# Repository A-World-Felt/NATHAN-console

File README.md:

# NATHAN Console

## How it began

The NATHAN console was born from a desire to create something meaningful for an incredible person: **Nathan Therrien**.

I met Nathan in high school. He was one of those rare people who naturally brighten the world around them. Always smiling, always the first to say hello, to crack a joke, to make everyone around him feel good. We shared the same class in our final year, and even then, I was amazed by his radiant energy.

After high school, life took us in different directions. But I kept following Nathan online, especially through his Facebook page, where he shares videos of his musical explorations. Because yes, on top of everything else, **Nathan is an outstanding musician** and a passionate synthesizer enthusiast.

One morning in year 2022, Nathan made a post looking for help with 3D printing and soldering. At that time, I was just diving into the world of programming, microcontrollers, and digital fabrication. I was eager to learn and build something real. The moment I saw his message, I knew: **this was the project I had been waiting for**.

Working with Nathan, someone I had admired for years, gave me the perfect opportunity to grow my skills while collaborating with someone truly inspiring. He would be part of the process: designing the sounds, shaping the ideas, and even learning to code. From the start, the goal was clear: **build something together that he could one day fully own**.

Since 2022, this journey has become a shared adventure. Today, I’m proud to present the first version of the console:
**NATHAN — Narrative Audio Terminal for Humans with Alternative Navigation**.

As time becomes more limited for me, my hope is to pass the torch. I want the community to take this project further, to make it bigger, better, and even more inclusive.

---

## What is NATHAN?

**NATHAN** is an open source game console powered by a Raspberry Pi Pico, specifically designed for blind or visually impaired players.

Inspired by the form of an Xbox controller, the device includes:

* 5 tactile buttons
* 5 LED indicators
* An integrated audio output
  Together, these features enable an immersive and fully accessible gaming experience.

---

## Features

* 🎮 **Ergonomic form** – Inspired by the Xbox controller for comfortable use
* 🔘 **5 physical buttons** – Easily distinguishable for gameplay
* 💡 **5 LED indicators** – Optional visual feedback
* 🔊 **Audio output** – For immersive, sound-based gameplay
* ♿ **Inclusive game design** – Every game is made for accessibility

---

## Game Concept

Each game on the NATHAN console features a **blind protagonist named Nathan**.

The current flagship game, **NATHAN: Glassbreaker**, puts you in the role of Nathan, a hero who fights and navigates *only* through sound. It's a game where your ears become your eyes, and audio becomes your primary interface with the world. A game felt instead of seen.

---

## Open Source & Community

NATHAN is proudly open source.

This project is a call to creators, developers, makers, and dreamers:
**Let’s build accessible games together.**

Whether you want to:

* Design new games tailored for blind players
* Improve the hardware or firmware
* Suggest ideas to enhance the console
  Your contribution is welcome.

---

## Name Meaning

> **NATHAN** = *Narrative Audio Terminal for Humans with Alternative Navigation*

A console built around sound, for a hero and a community that navigates the world differently.

---

> 🎙️ *Together, let’s make gaming accessible to everyone.*

---

## 📚 Documentation & gouvernance

Toute la documentation projet vit dans [`docs/`](./docs/) :

- **[`docs/README.md`](./docs/README.md)** — *commencez ici* (parcours de lecture).
- **[Journal des décisions — ADR](./docs/decisions/README.md)** — *pourquoi* le projet est ainsi, et son évolution dans le temps.
- **[Specs](./docs/specs/)** · **[Planification & GANTT](./docs/planning/)** · **[Architecture](./docs/architecture/)**.
- **[CONTRIBUTING.md](./CONTRIBUTING.md)** — comment contribuer et **tracer une décision**.
- **[Étude matérielle Pi 3 A+ / deux PCB](./hardware/pi3a-prototype/README.md)** — proposition Codex en cours de revue, avec schémas et placements ; statut exact des validations indiqué dans le dossier.

---

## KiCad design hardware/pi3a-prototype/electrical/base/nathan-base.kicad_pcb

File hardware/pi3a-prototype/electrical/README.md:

> État figé et résultats de référence : [README D1-3](../README.md). Les points de conception ci-dessous restent des propositions, distinctes des essais matériels.

# Schémas D1 — connexions proposées pour revue

Auteur : Codex/OpenAI `nathan_bom`. Les projets `controls/nathan-controls.kicad_pro` et `base/nathan-base.kicad_pro` contiennent des schémas KiCad 8 éditables. Les symboles fonctionnels locaux portent des broches numérotées ; leurs connexions sont nommées explicitement. `design-networks.json`, `pin-map.csv` et `bom-proposal.csv` détaillent la source et la limite de chaque proposition.

La carte commandes comprend **93 composants physiques proposés et 4 déclarations ERC**, répartis entre interface, entrées numériques, entrées analogiques, multiplexeur, cinq branches haptiques et buck. Son ERC natif actuel rapporte **0 violation**. L’export natif initial, comparé au modèle broche par broche, ne présentait aucune connexion divergente ou absente. Un ERC réussi ne remplace ni la vérification du dessin fabricant, ni le dimensionnement thermique, ni les essais du matériel.

La porteuse D1 comprend **88 composants physiques proposés**, dont circuits audio et USB-C ; leur qualification reste à faire. Les nets `USB_PC_VBUS`, `USB_CHARGE_LIMITED` et `5V_SYS` restent distincts. Aucun fil artificiel ne remplace les protections et contrôles manquants. Le projet PCB D0.1 est une étude de placement séparée : **le checkpoint D1-3 comporte des commandes routées et une porteuse placée avec 257 liaisons encore ouvertes**.

## Choix proposés à partir des données connues

| Choix D1 | Motif et limite |
|---|---|
| MCP3208-CI/SL à la place du MCP3008 | Résolution 12 bits conforme au texte du cahier des charges. Brochage SOIC-16 vérifié ; trames SPI/logiciel à adapter. Ce remplacement n’est pas effectué dans le classeur original. |
| L2/R2 analogiques | Variante cohérente avec les deux potentiomètres envisagés dans le BOM ; elle conserve 14 entrées numériques avec L1/R1 et les clics des sticks. Technologie mécanique/capteur à sélectionner. |
| MCP23017-E/SO, 14 entrées seulement | Les broches GPA7/GPB7 restent inutilisées comme entrées ; configuration en sorties basses prévue. INTA porte l’interruption miroir ; INTB reste libre. |
| TCA9548APWR, adresse 0x70 | Cinq branches pour les cinq DRV2604L à 0x5A ; une branche sélectionnée par transaction. |
| DRV2604LDGSR | Brochage DGS vérifié. REG et VDD découplés, IN/TRIG à la masse, EN au rail haptique ; chaque moteur reste connecté entre les deux sorties différentielles. |
| Logique sur 3V3_PI, moteurs sur buck séparé | Aucun parallélisme entre régulateurs 3,3 V. Les pull-up aval suivent le rail moteur ; séquencement des alimentations encore à vérifier. |
| TPS62080DSGR conservé | Diviseur 249 kΩ/39,2 kΩ : 3,308 V nominal. Inductance 1 µH et condensateurs selon l’application TI, avec qualification des références/dérating encore requise. |
| Nappe GPIO polarisée | La porteuse inférieure ne peut pas être supposée enfichable sous le Pi : le PiSugar occupe cette zone par ses contacts pogo et le GPIO du Pi est dirigé vers le haut. La nappe préserve démontabilité et séparation des supports. |

Les broches 15/16 du connecteur intercartes D1 deviennent `3V3_PI` et `CTRL_RESET_N` ; elles étaient réservées dans D0.1. Ne pas fabriquer ni mélanger une nappe et une carte à partir de révisions différentes. Le fichier historique `pcb/interboard-interface.csv` décrit encore D0 ; le contrat D1 fait foi dans `pin-map.csv`, références J100 des deux cartes.

Le démarrage logiciel doit configurer l’extension, les interruptions, la sélection du multiplexeur et le mode LRA. La consigne VG0832013D reste 1,8 Vrms ; alimenter le driver en 3,3 V ne définit pas sa consigne moteur. SPI à 100 kHz et conversion d’amorçage après changement de voie sont proposés pour qualifier le filtre d’entrée ; aucune précision effective de 12 bits n’est garantie par le seul nombre de bits du composant.

## Sources vérifiées

- [Microchip MCP3208, DS21298E](https://ww1.microchip.com/downloads/en/DeviceDoc/21298e.pdf), tableau 3-1 page 15 et acquisition pages 17–18.
- [Microchip MCP23017, DS20001952D](https://ww1.microchip.com/downloads/aemDocuments/documents/APID/ProductDocuments/DataSheets/MCP23017-Data-Sheet-DS20001952.pdf), pages 1 et 11.
- [TI TCA9548A, SCPS207H](https://www.ti.com/lit/ds/symlink/tca9548a.pdf), brochage page 3.
- [TI DRV2604L, SLOS866F](https://www.ti.com/lit/ds/symlink/drv2604l.pdf), DGS page 4.
- [TI TPS62080, SLVSAE8F](https://www.ti.com/lit/ds/symlink/tps62080.pdf), pages 4, 12–14 et 19.

## Ce qu’il reste avant une carte complète

1. Qualifier les connecteurs/câbles et les références passives, terminer les empreintes de l’inductance et des commandes physiques.
2. Réaliser la chaîne casque, sa commande de volume/mute et son alimentation ; PCM5102A seul reste une sortie ligne.
3. Définir le circuit du port commun : courant d’entrée autorisé selon la source, blocage inverse, détection VBUS, protection ESD et raccordement USB périphérique du Pi.
4. Reporter la netlist finale aux PCB, adapter le placement, router puis vérifier chaque carte et sa correspondance au schéma.
5. Valider l’empilement réel et les mouvements dans l’assemblage, puis effectuer les essais électriques/thermiques/USB/autonomie.

Les éléments bloqués sont précisément visibles dans les connecteurs et notes du schéma. Ils ne sont ni masqués par des réserves présentées comme pièces réelles ni remplacés par des pistes arbitraires.

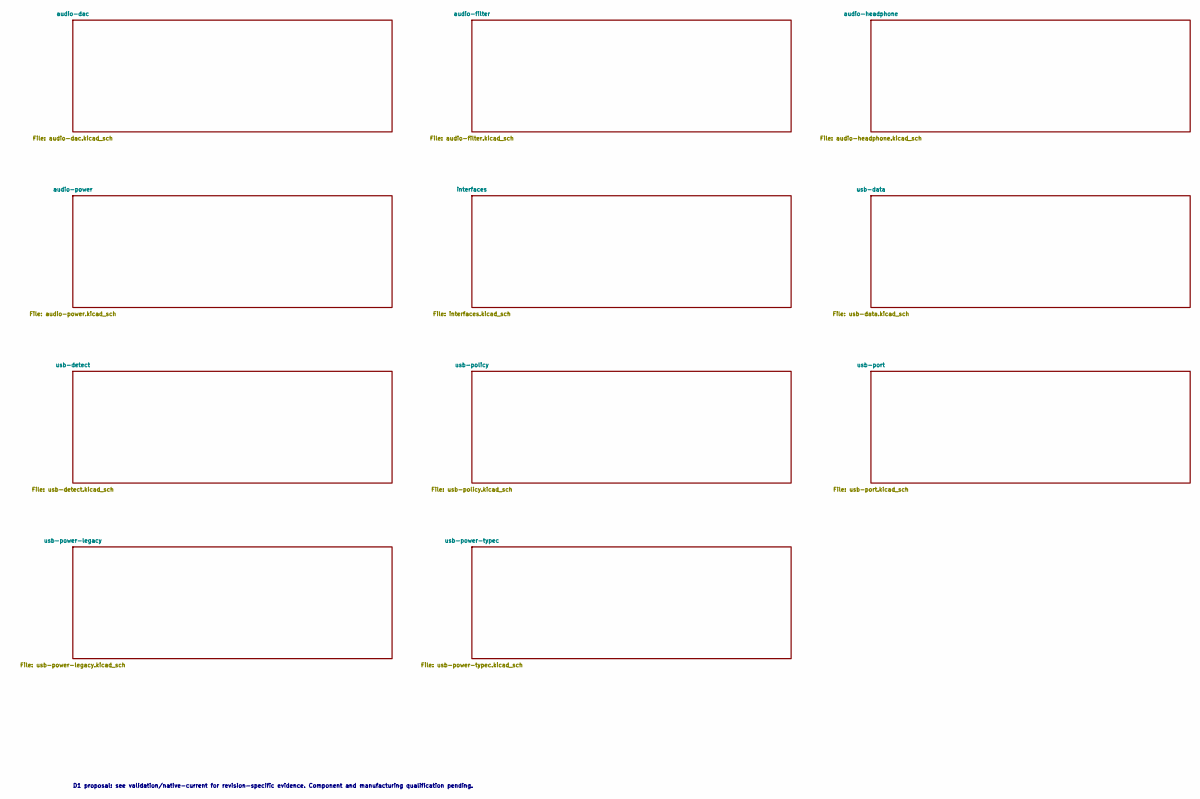
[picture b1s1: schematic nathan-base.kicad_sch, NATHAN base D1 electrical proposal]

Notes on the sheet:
D1 proposal: see validation/native-current for revision-specific evidence. Component and manufacturing qualification pending.

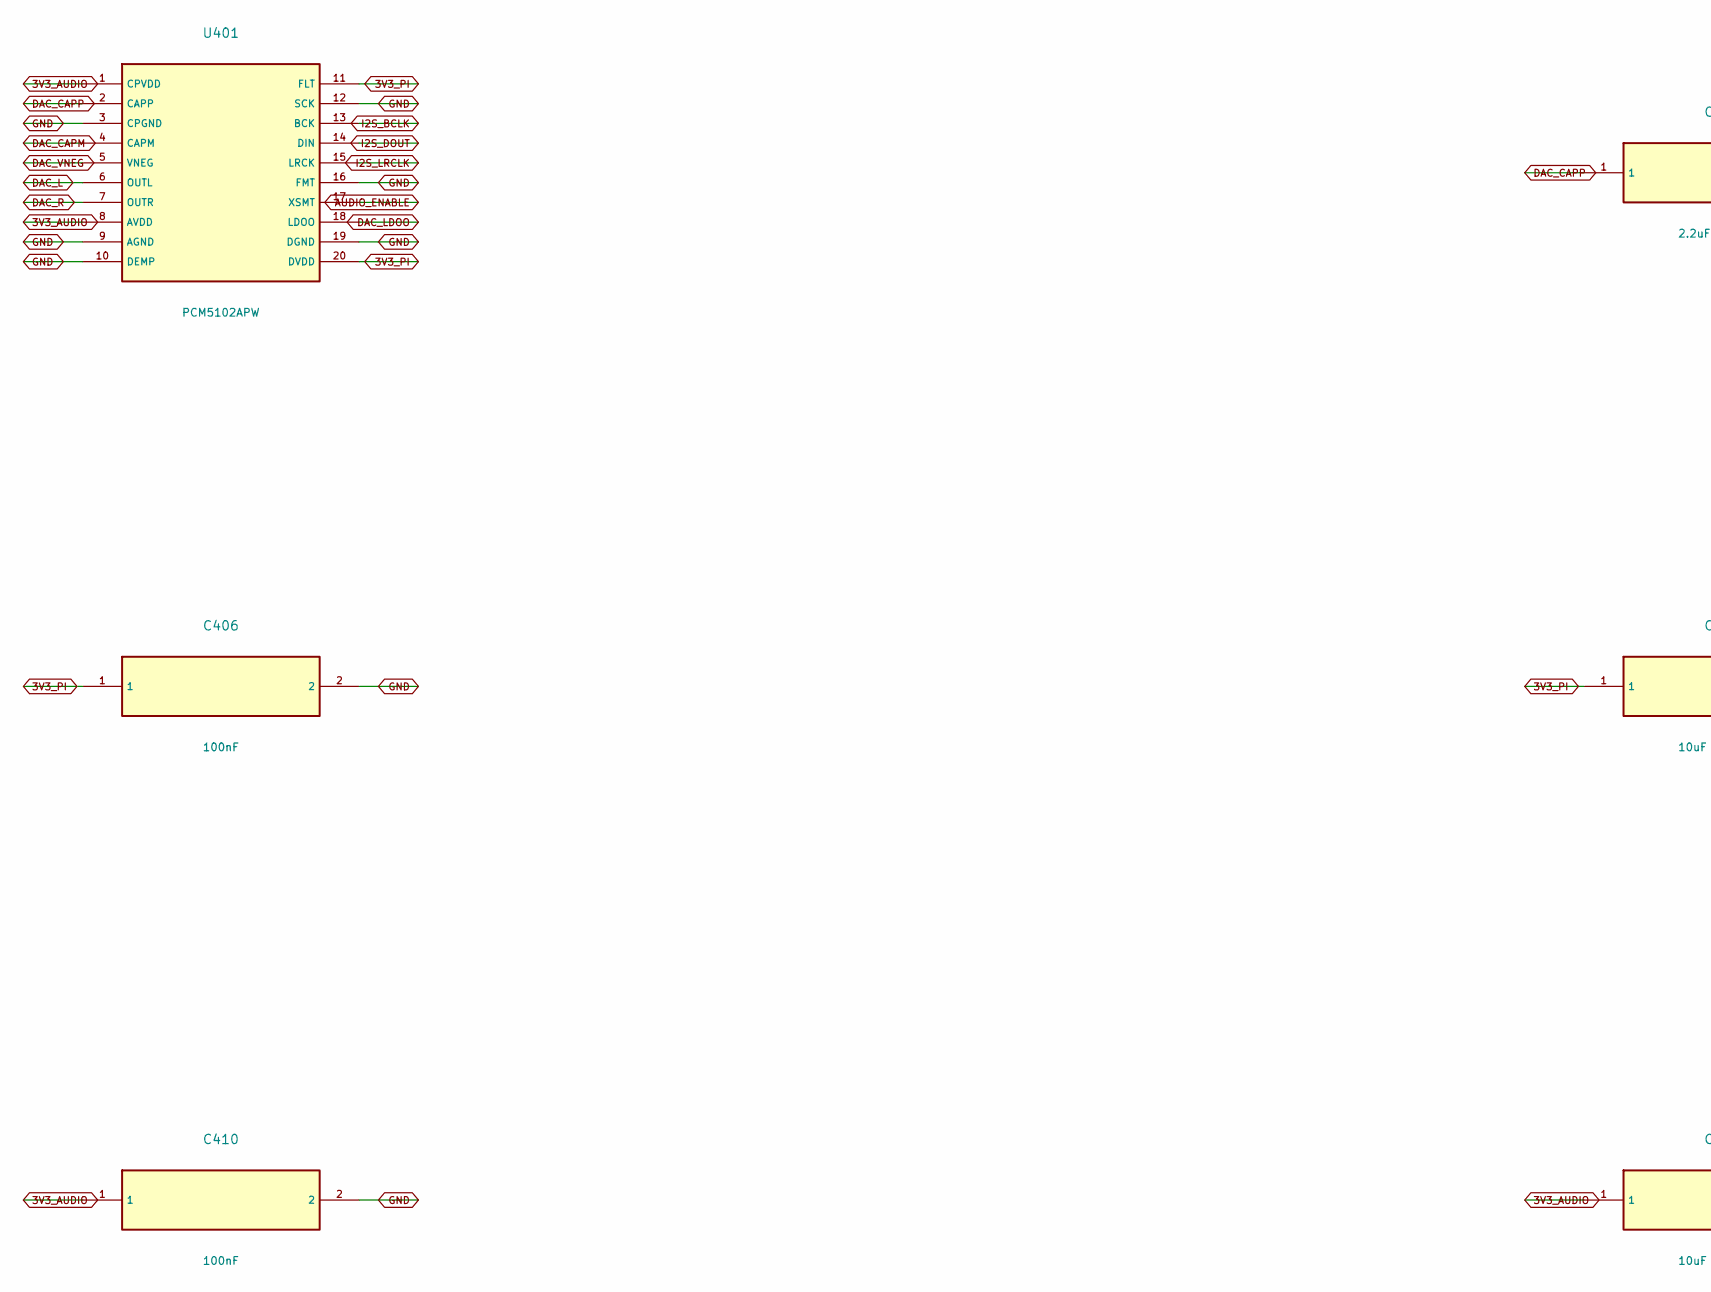
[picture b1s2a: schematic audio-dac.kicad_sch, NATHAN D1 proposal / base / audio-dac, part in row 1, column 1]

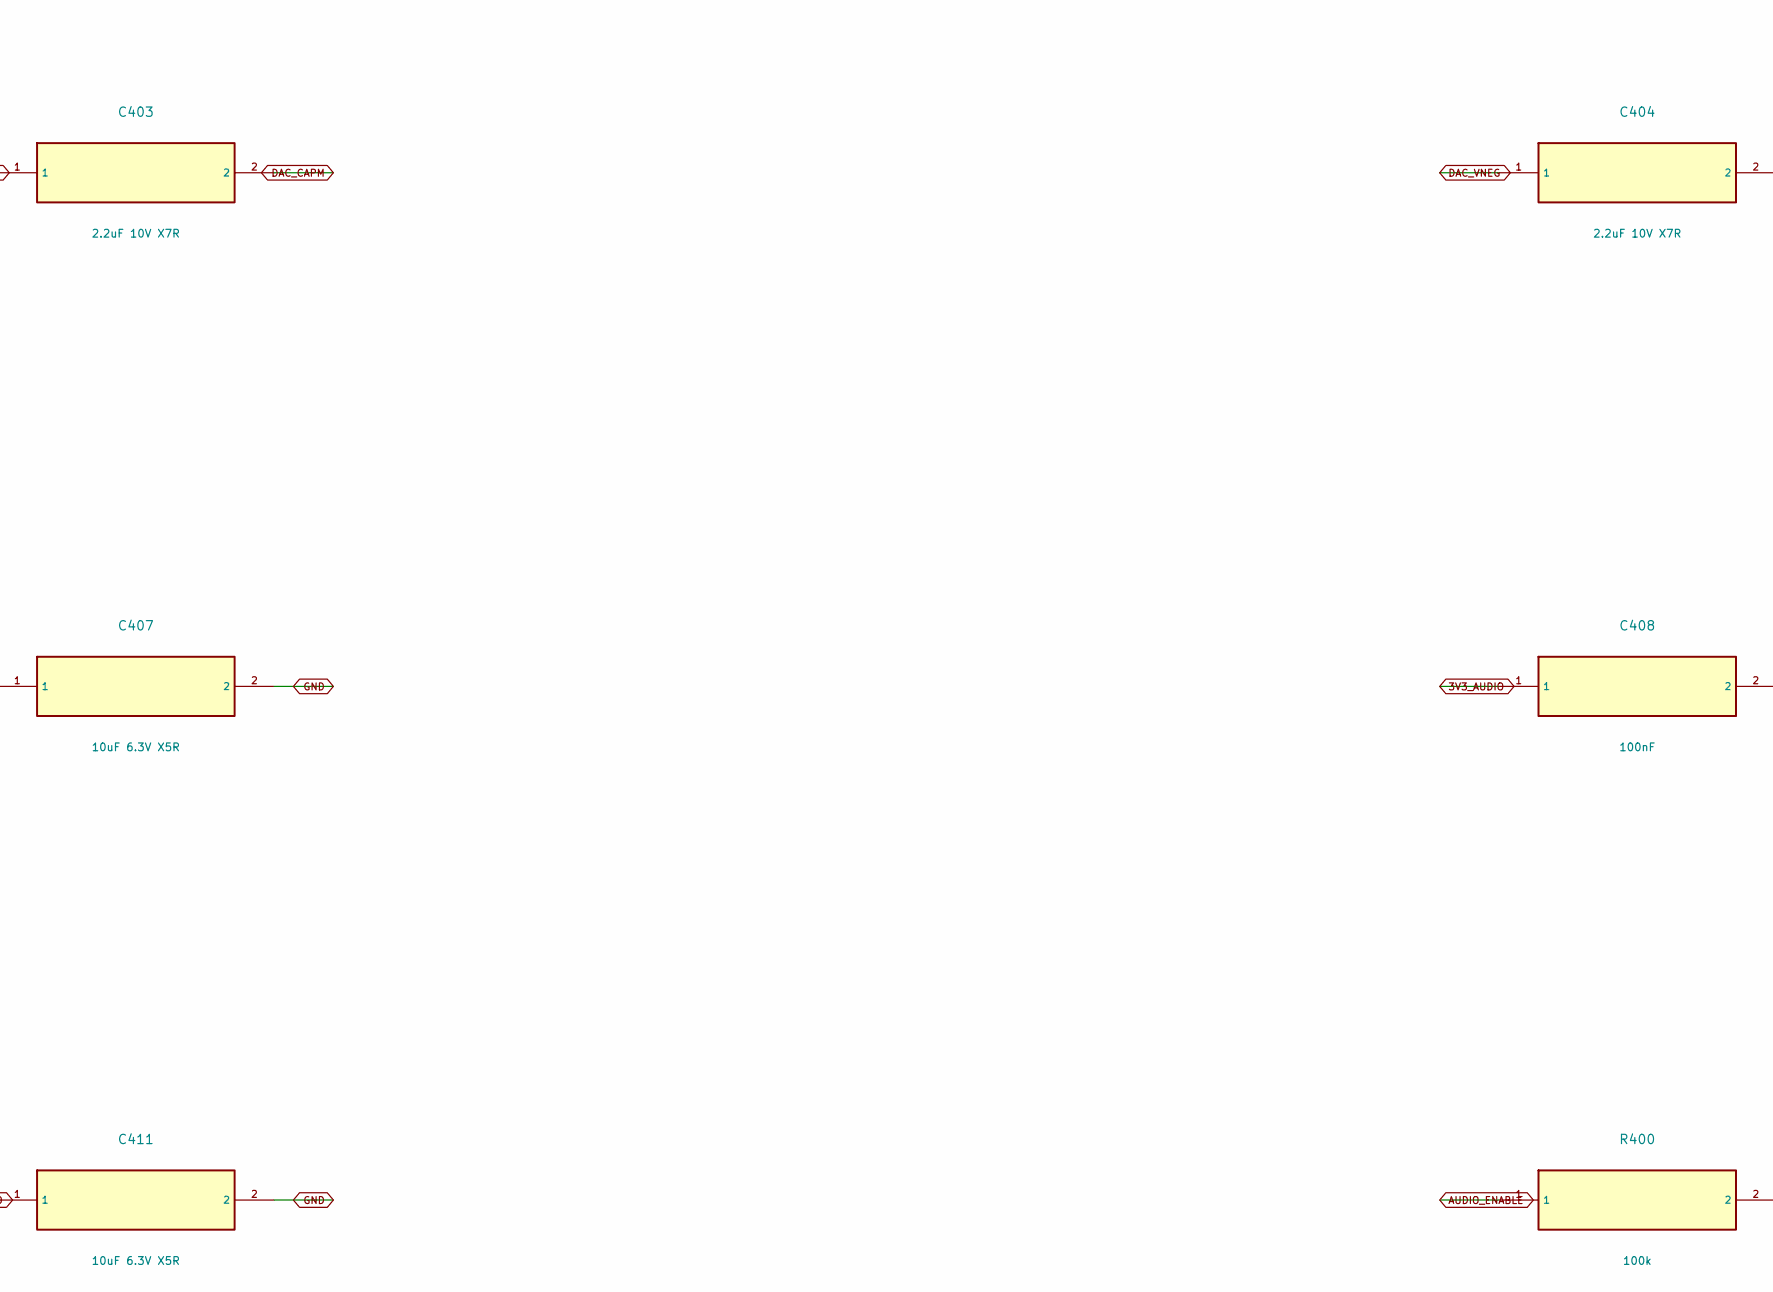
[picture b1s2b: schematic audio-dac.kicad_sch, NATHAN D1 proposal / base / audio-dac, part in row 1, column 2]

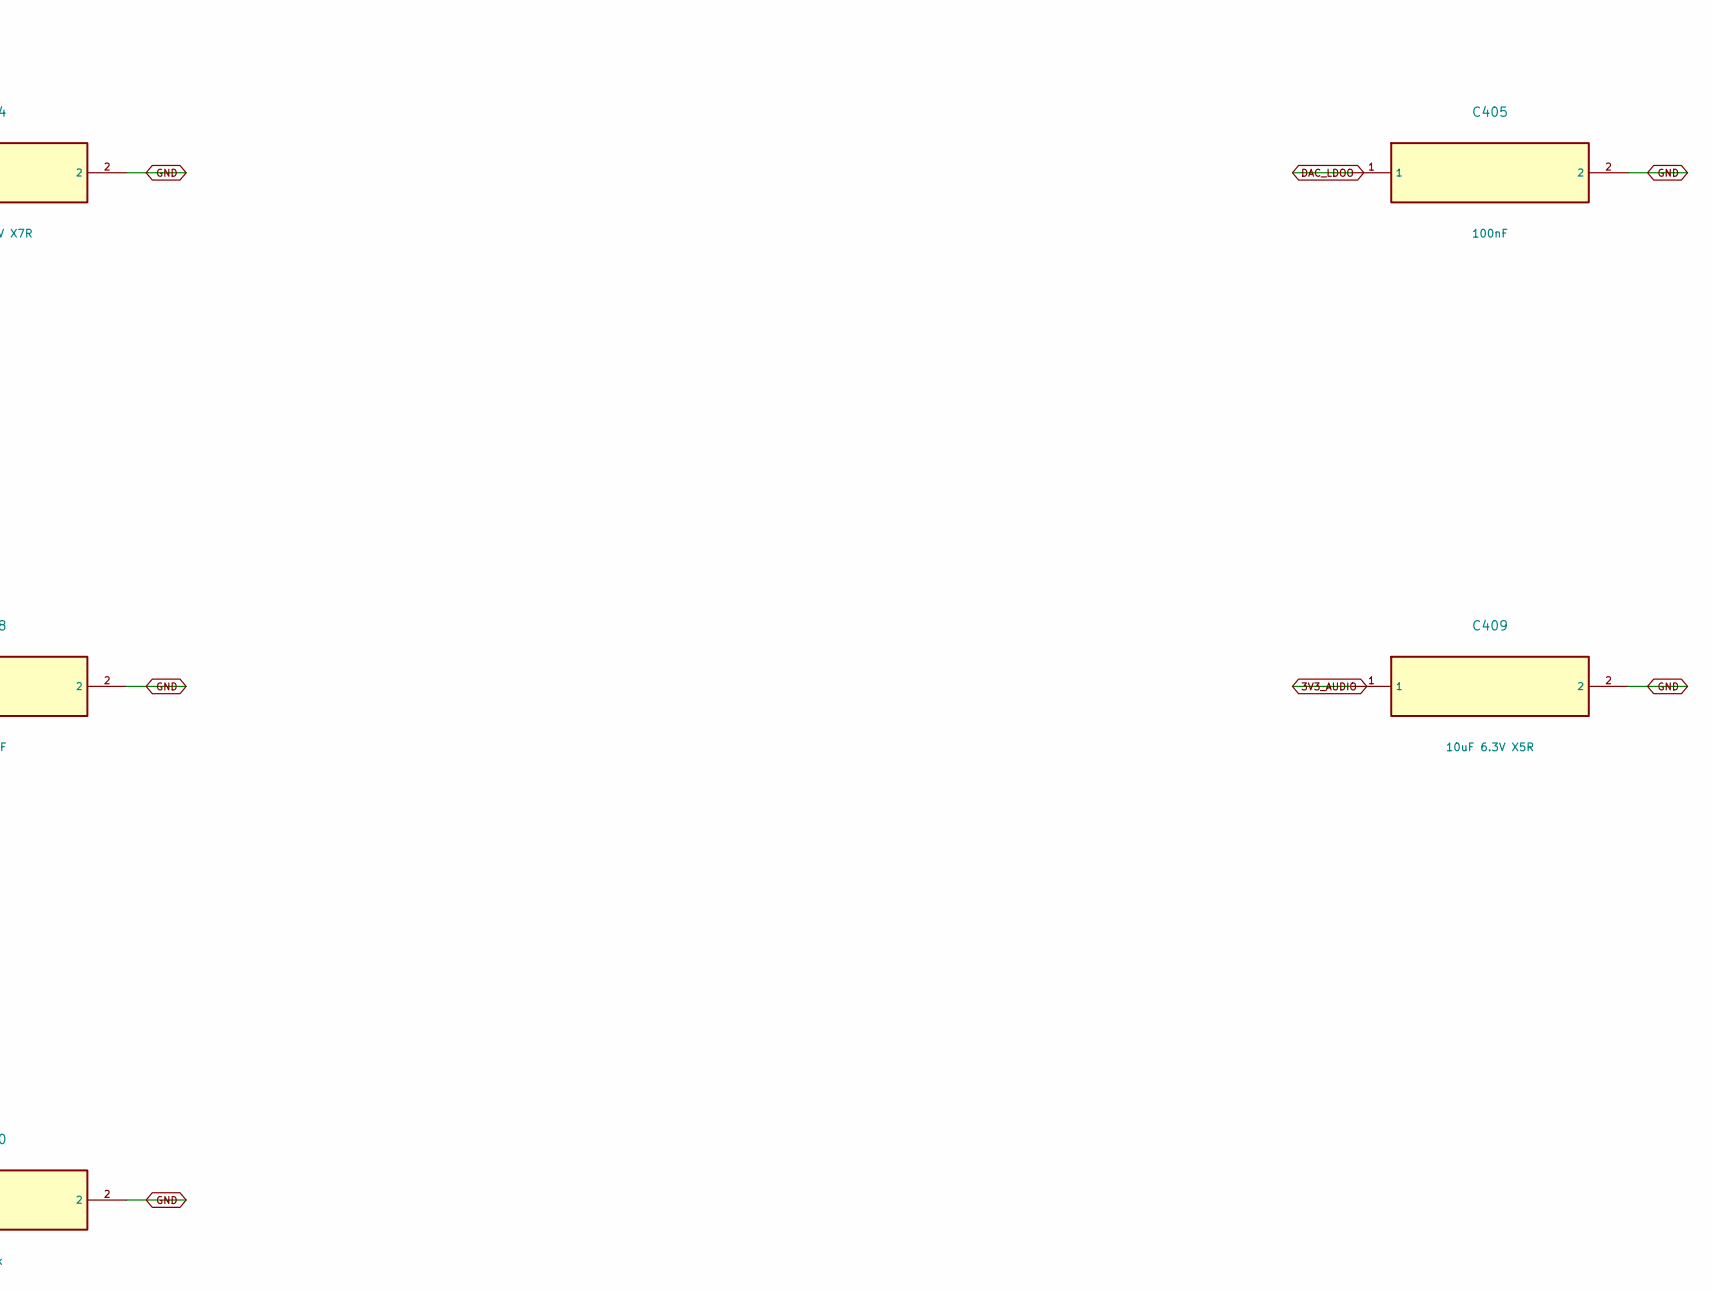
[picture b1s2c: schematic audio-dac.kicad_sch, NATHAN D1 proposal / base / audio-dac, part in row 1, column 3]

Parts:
C403, C404: 2.2uF 10V X7R; C_0603_1608Metric
C405, C406, C408, C410: 100nF; C_0603_1608Metric
C407, C409, C411: 10uF 6.3V X5R; C_0603_1608Metric
R400: 100k; R_0603_1608Metric
U401: PCM5102APW; TSSOP-20_4.4x6.5mm_P0.65mm

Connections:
3V3_AUDIO: C408.1, C409.1, C410.1, C411.1, U401.1 (CPVDD), U401.8 (AVDD); also elsewhere on the board
3V3_PI: C406.1, C407.1, U401.11 (FLT), U401.20 (DVDD); also elsewhere on the board
AUDIO_ENABLE: R400.1, U401.17 (XSMT); also elsewhere on the board
DAC_CAPM: C403.2, U401.4 (CAPM)
DAC_CAPP: C403.1, U401.2 (CAPP)
DAC_L: U401.6 (OUTL); also elsewhere on the board
DAC_LDOO: C405.1, U401.18 (LDOO)
DAC_R: U401.7 (OUTR); also elsewhere on the board
DAC_VNEG: C404.1, U401.5 (VNEG)
GND: C404.2, C405.2, C406.2, C407.2, C408.2, C409.2, C410.2, C411.2, R400.2, U401.3 (CPGND), U401.9 (AGND), U401.10 (DEMP), U401.12 (SCK), U401.16 (FMT), U401.19 (DGND); also elsewhere on the board
I2S_BCLK: U401.13 (BCK); also elsewhere on the board
I2S_DOUT: U401.14 (DIN); also elsewhere on the board
I2S_LRCLK: U401.15 (LRCK); also elsewhere on the board

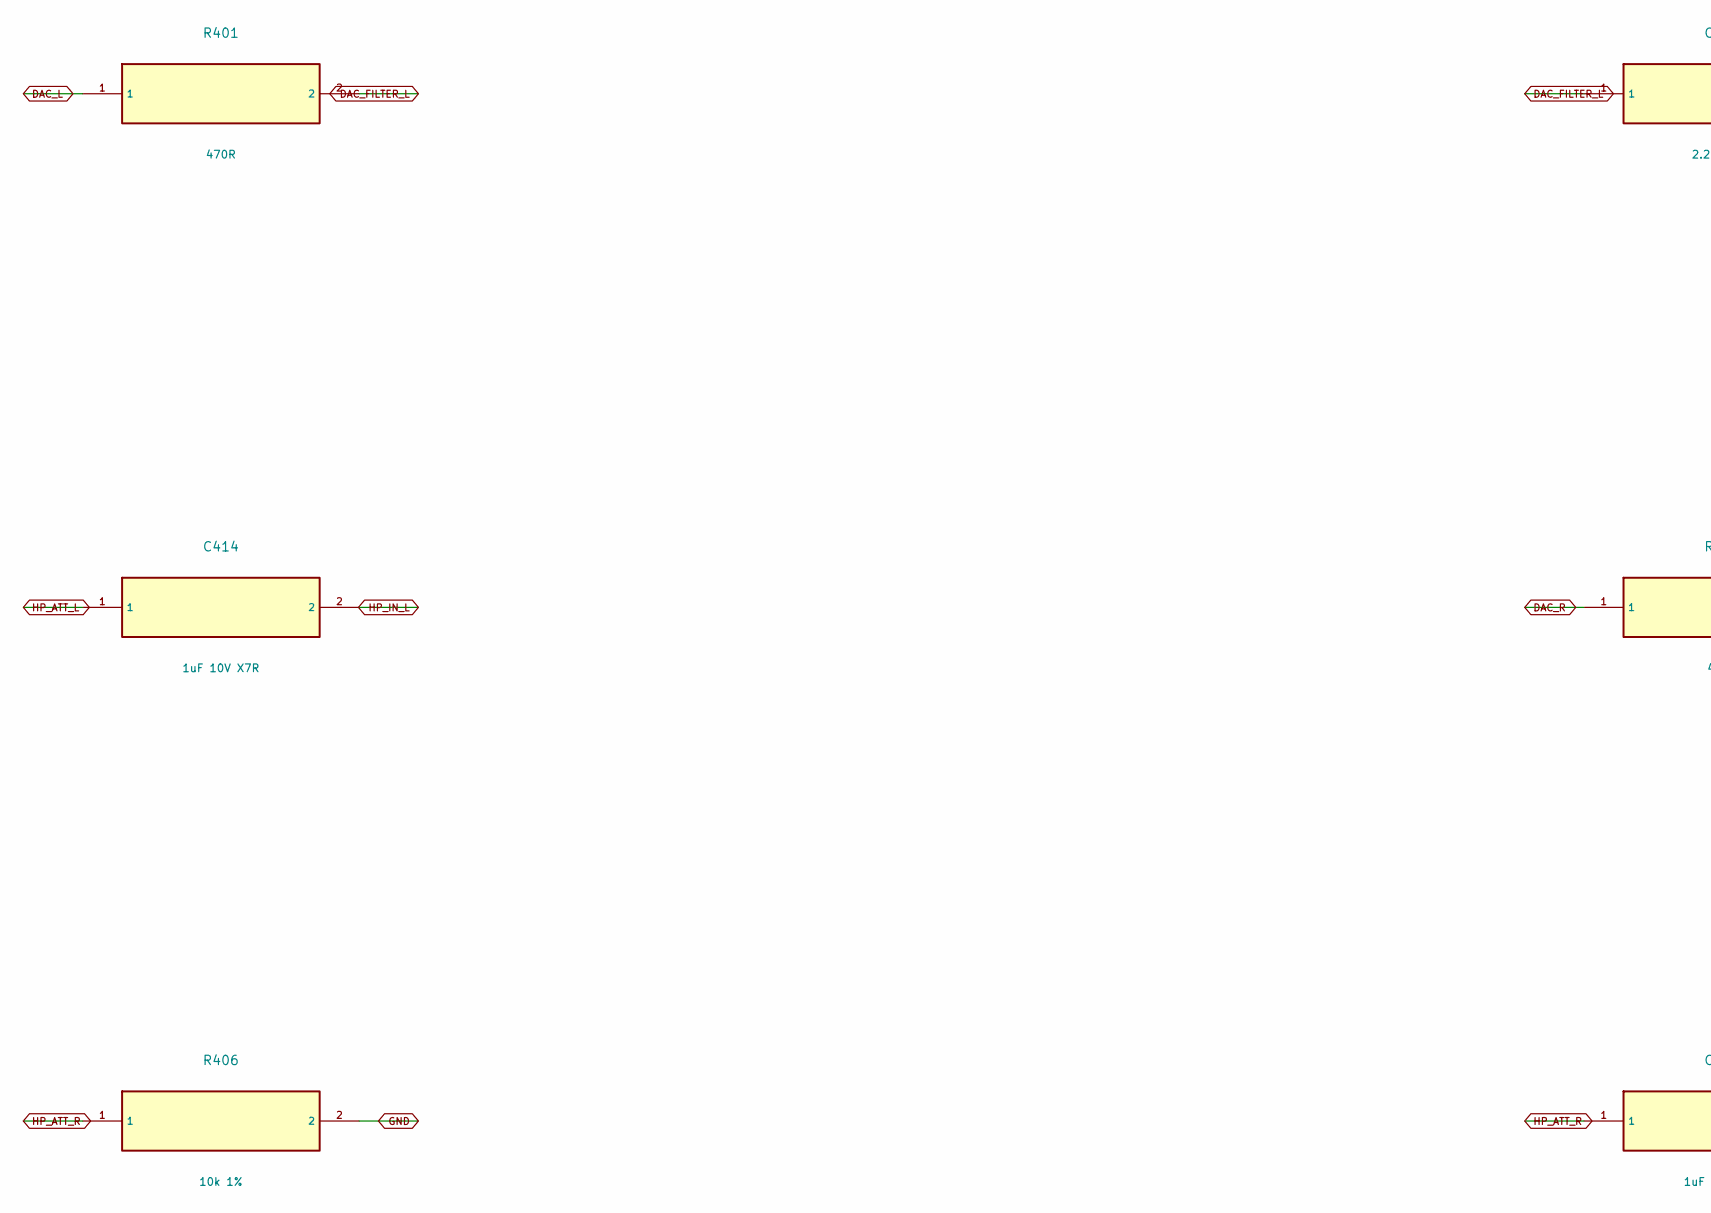
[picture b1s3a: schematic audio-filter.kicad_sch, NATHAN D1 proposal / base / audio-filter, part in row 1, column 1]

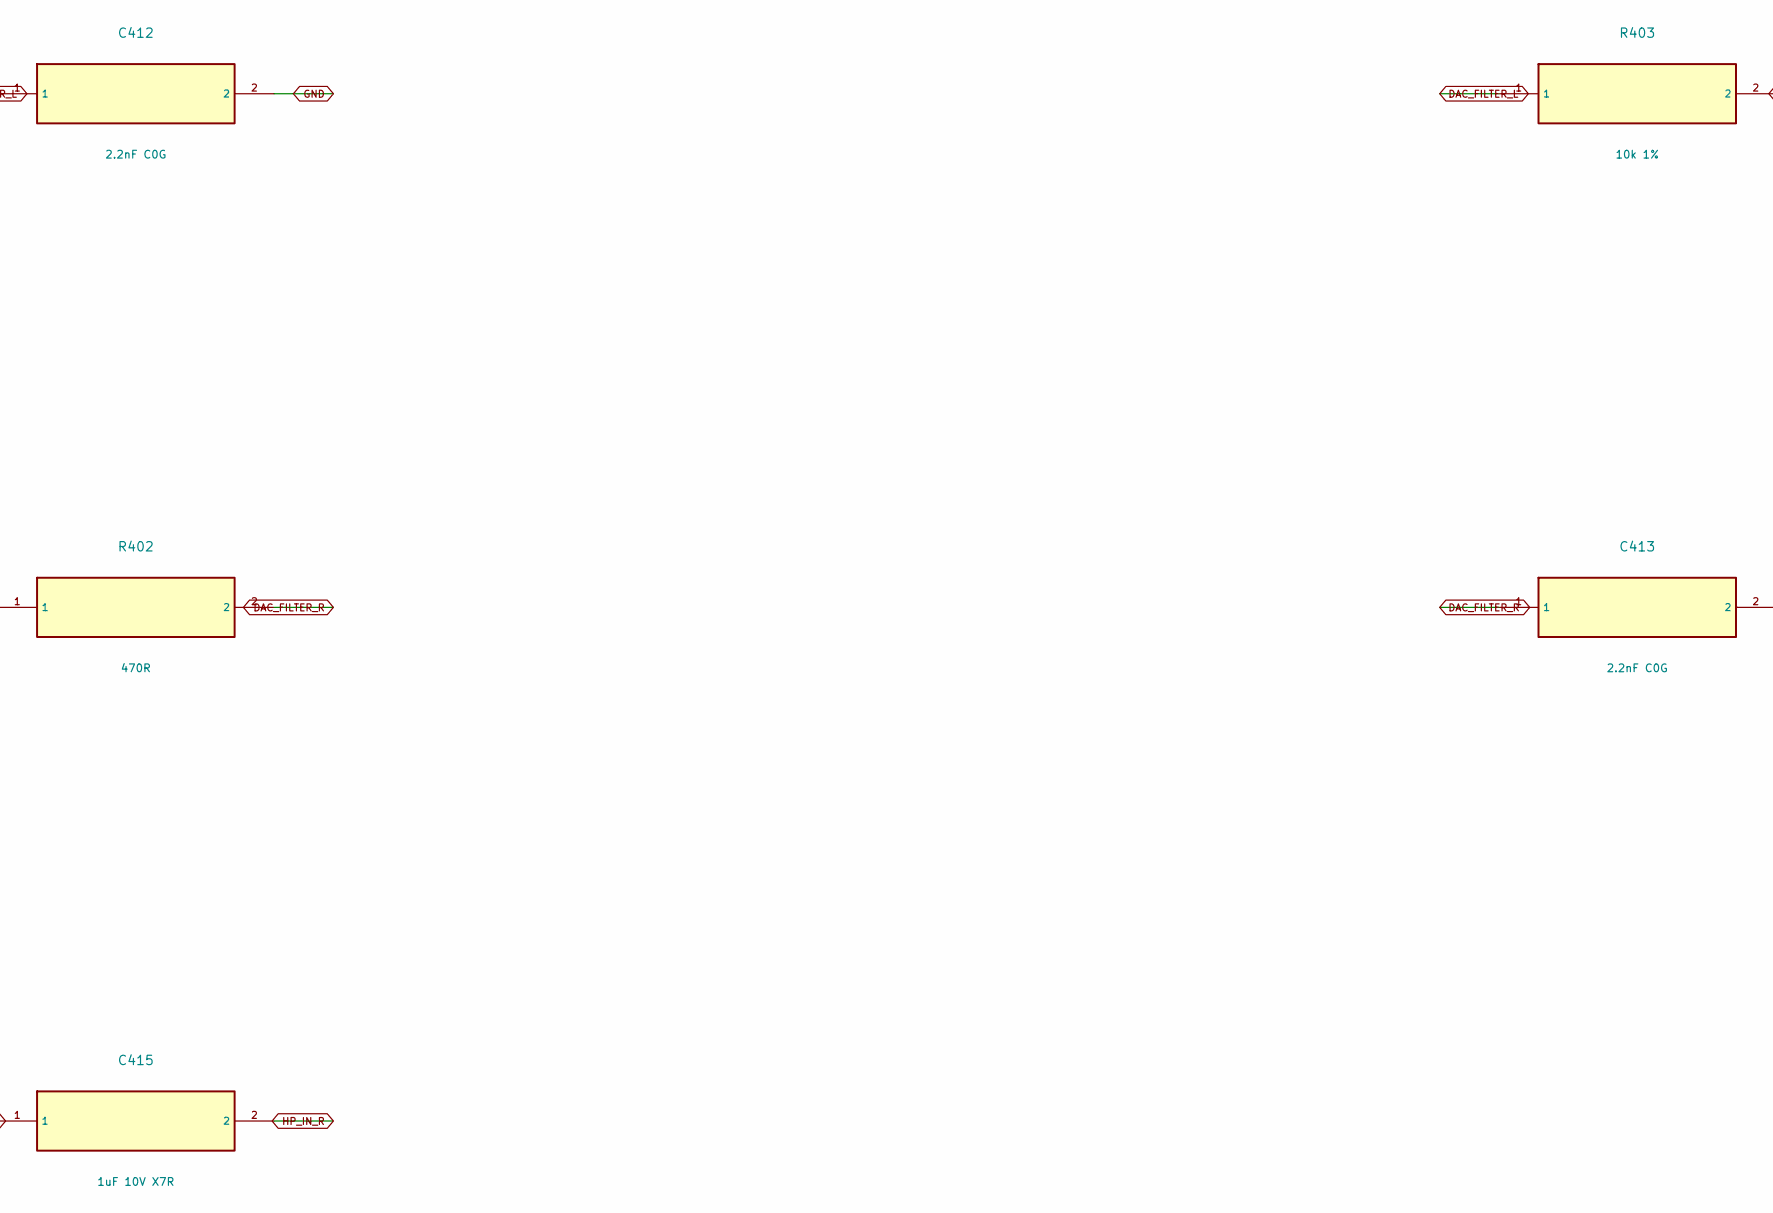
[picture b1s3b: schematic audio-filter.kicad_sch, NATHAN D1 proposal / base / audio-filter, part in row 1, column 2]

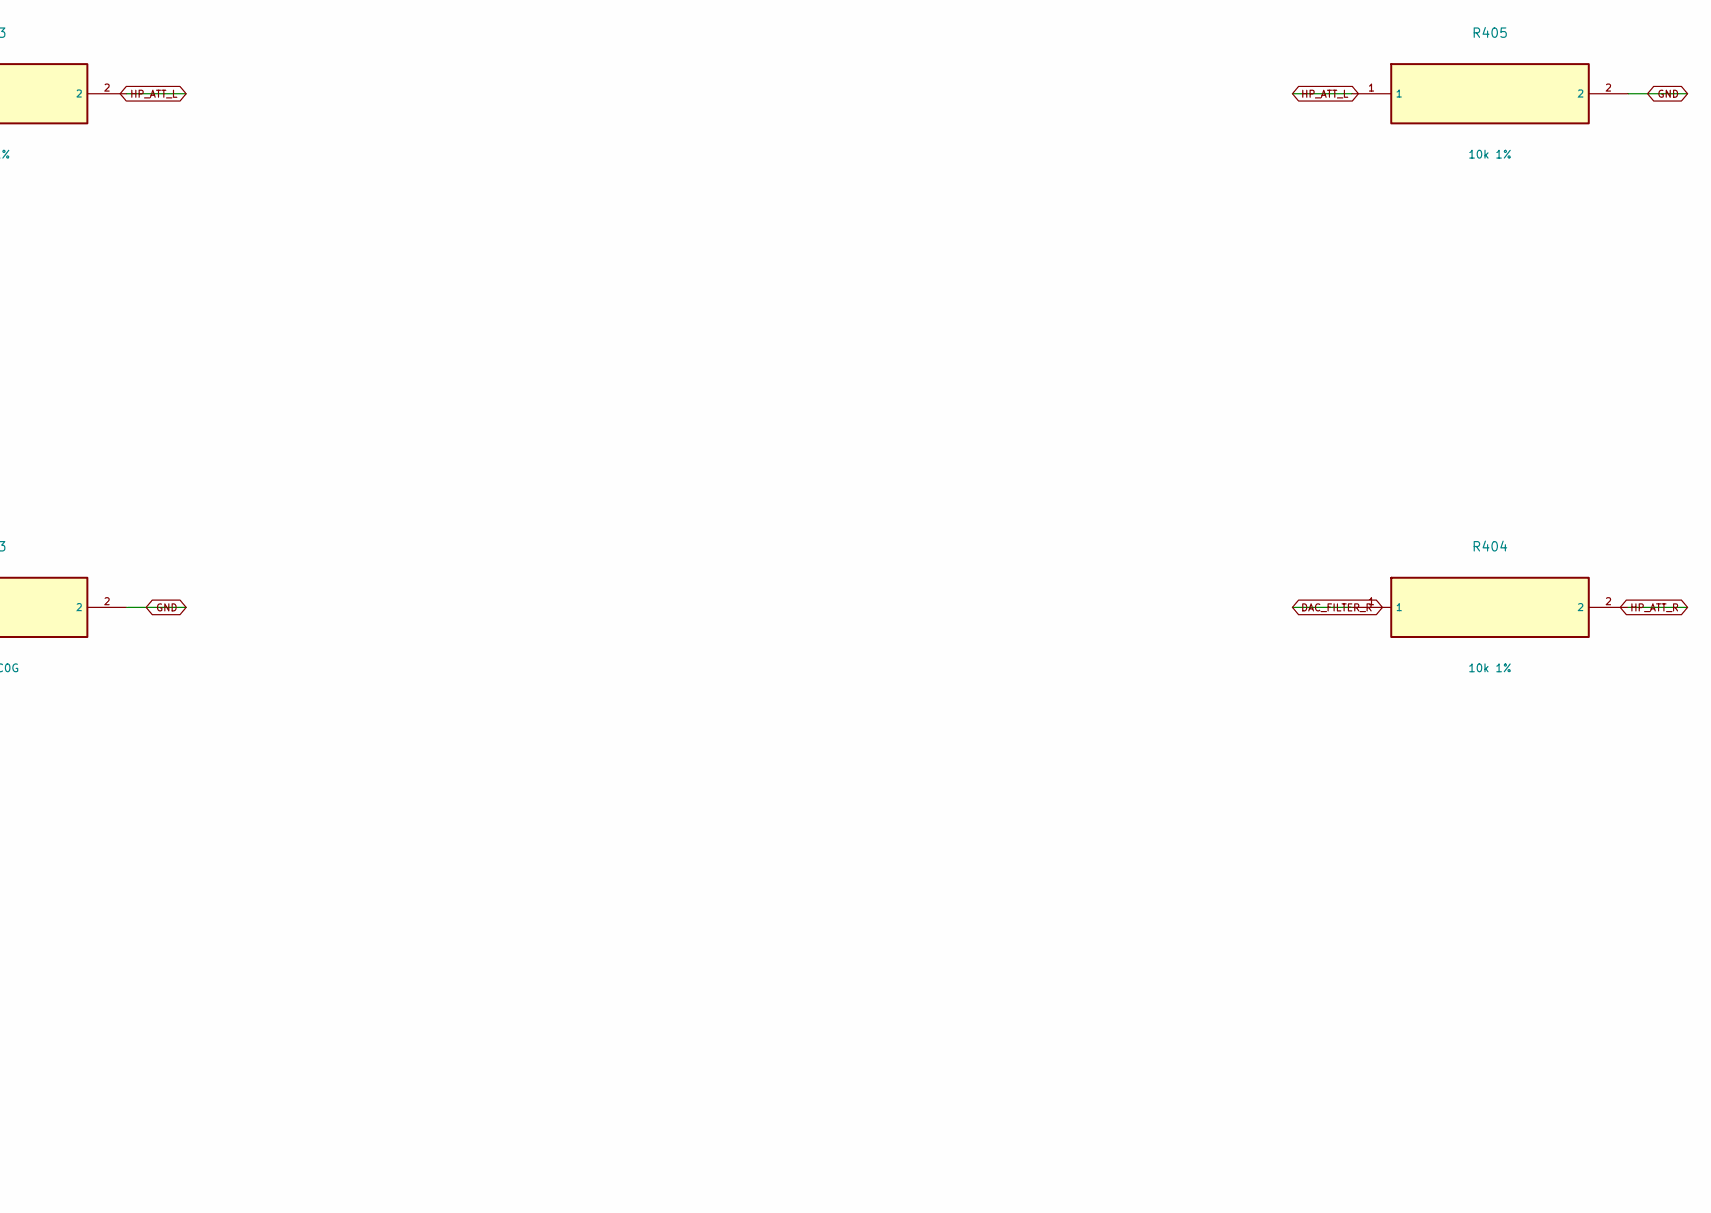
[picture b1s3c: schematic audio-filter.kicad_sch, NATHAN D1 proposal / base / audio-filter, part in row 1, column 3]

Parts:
C412, C413: 2.2nF C0G; C_0603_1608Metric
C414, C415: 1uF 10V X7R; C_0603_1608Metric
R401, R402: 470R; R_0603_1608Metric
R403, R404, R405, R406: 10k 1%; R_0603_1608Metric

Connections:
DAC_FILTER_L: C412.1, R401.2, R403.1
DAC_FILTER_R: C413.1, R402.2, R404.1
DAC_L: R401.1; also elsewhere on the board
DAC_R: R402.1; also elsewhere on the board
GND: C412.2, C413.2, R405.2, R406.2; also elsewhere on the board
HP_ATT_L: C414.1, R403.2, R405.1
HP_ATT_R: C415.1, R404.2, R406.1
HP_IN_L: C414.2; also elsewhere on the board
HP_IN_R: C415.2; also elsewhere on the board
